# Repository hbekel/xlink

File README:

XLINK -- Bidirectional 8-bit parallel data transfers between PS/2
Parallel Port and C64 User Port with optional reset circuit

---------------------------------------------------------------------
Introduction
---------------------------------------------------------------------

XLINK is a system for fast 8-bit parallel data transfers between a C64
and an IBM-PC using a either a parallel port cable or a simple USB
device connected to the C64 user port.

A command-line client on the PC side is used to send data or commands
to an interrupt-driven server installed on the C64. It is possible to
load data from disk into C64 memory, save C64 memory content to disk,
to peek and poke values to and from C64 memory, run BASIC programs,
jump to memory addresses, and force a hardware reset of the C64.

Different options exists to install the server on the C64, from a
simple server.prg that needs to be loaded on the C64 prior to use, or
a permanent solution that integrates a server in a modified kernal or
a simple eprom cartridge.

The underlying communication protocol is implemented in a shared
library, allowing you to use and extend xlink's functionality for your
own programs.

----------------------------------------------------------------------
Cable
----------------------------------------------------------------------

The XLINK cable is a simple 8-bit parallel transfer cable connecting
the PC Parallel Port to the C64 User port.

       ---------------------------------------------
       PC Parallel Port   |     C64 User Port
       ---------------------------------------------
       GND    (18-25)    <->    GND    (1, 12, A, N)
       D0     (2)        <->    PB0    (C) 
       D1     (3)        <->    PB1    (D) 
       D2     (4)        <->    PB2    (E) 
       D3     (5)        <->    PB3    (F) 
       D4     (6)        <->    PB4    (H) 
       D5     (7)        <->    PB5    (J) 
       D6     (8)        <->    PB6    (K) 
       D7     (9)        <->    PB7    (L) 
       BUSY   (11)       <--    PA2    (M) 
       STROBE (1)        -->    /FLAG2 (B) 

A shielded cable is recommended. The cable shield should be connected
to shield ground on both sides. A 0.1uF capacitor between shield and
ground at the c64 side can also help to reduce noise. Improper
shielding will most likely cause transfer errors.

CAUTION: There is no protection of any kind. The parallel port pins
are directly connected to port B of CIA2. Always power down both the
PC and C64 before inserting/removing the cable. Also turn off the C64
during boot, reboot or shutdown of the PC.

----------------------------------------------------------------------
Optional Reset Circuit
----------------------------------------------------------------------

This small circuit can be used to force a hardware reset of the C64
when the INIT line at the parallel port is pulled low.
                  
 INIT                      +5V                          
  o                         o                                          
  |      ____               |                                  
  o-----|____|--------------o       o RESET                                    
  |      10k                |       |                                      
  |                 ____    |       |                                    
  |            ----|____|---'       |                                       
  |            |    1.5k            |                                   
  |            |                 |  C                        
  |            |                 | /                                       
  |         |  C-----------------|B                                             
  |  ____   | /                  | \                                            
  '-|____|--|B                   |  E                                          
     10k    | \                     |                       
            |  E                    |                                          
               |                    |                                       
               o                    o                                       
              GND                  GND                                      

INIT is pin 16 at the parallel port, RESET is pin 3 at the user port.
GND and +5V can safely be taken from the user port as well.
Use BC547A or equivalent transistors.

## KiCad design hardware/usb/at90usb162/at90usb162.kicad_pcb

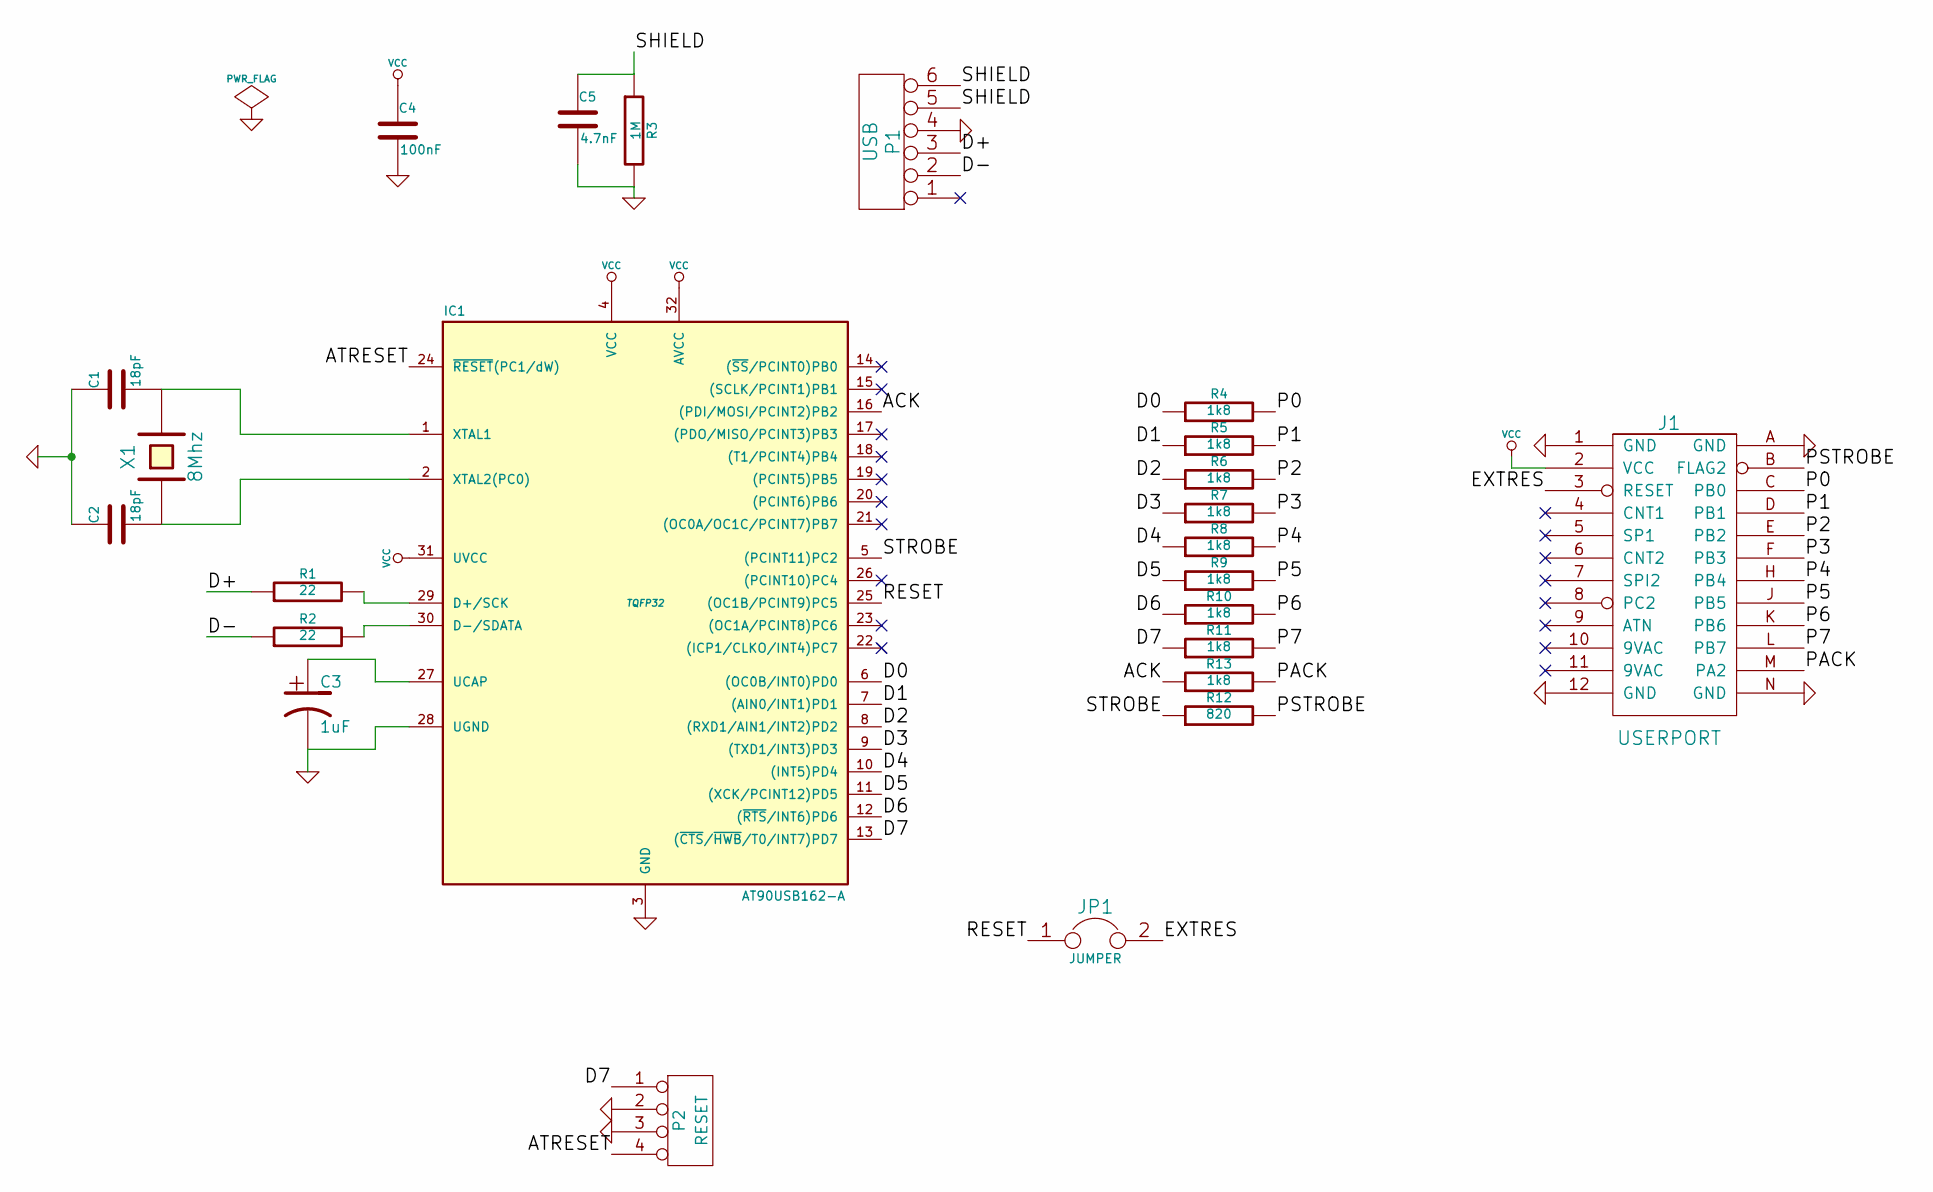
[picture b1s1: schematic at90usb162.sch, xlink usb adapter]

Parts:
C1, C2: 18pF
C3: 1uF
C4: 100nF
C5: 4.7nF
IC1: AT90USB162-A; TQFP32
J1: USERPORT
JP1: JUMPER
P1: USB
P2: RESET
R1, R2: 22
R3: 1M
R4, R5, R6, R7, R8, R9, R10, R11, R13: 1k8
R12: 820
X1: 8Mhz

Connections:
/ACK: IC1.16 ((PDI/MOSI/PCINT2)PB2), R13.1
/ATRESET: IC1.24 (~RESET~(PC1/dW)), P2.4
/D0: IC1.6 ((OC0B/INT0)PD0), R4.1
/D1: IC1.7 ((AIN0/INT1)PD1), R5.1
/D2: IC1.8 ((RXD1/AIN1/INT2)PD2), R6.1
/D3: IC1.9 ((TXD1/INT3)PD3), R7.1
/D4: IC1.10 ((INT5)PD4), R8.1
/D5: IC1.11 ((XCK/PCINT12)PD5), R9.1
/D6: IC1.12 ((~RTS~/INT6)PD6), R10.1
/D7: IC1.13 ((~CTS~/~HWB~/T0/INT7)PD7), P2.1, R11.1
/D+: P1.3, R1.1
/D-: P1.2, R2.1
/EXTRES: J1.3 (RESET), JP1.2
/P0: J1.C (PB0), R4.2
/P1: J1.D (PB1), R5.2
/P2: J1.E (PB2), R6.2
/P3: J1.F (PB3), R7.2
/P4: J1.H (PB4), R8.2
/P5: J1.J (PB5), R9.2
/P6: J1.K (PB6), R10.2
/P7: J1.L (PB7), R11.2
/PACK: J1.M (PA2), R13.2
/PSTROBE: J1.B (FLAG2), R12.2
/RESET: IC1.25 ((OC1B/PCINT9)PC5), JP1.1
/SHIELD: C5.1, P1.5, P1.6, R3.1
/STROBE: IC1.5 ((PCINT11)PC2), R12.1
GND: C1.1, C2.1, C3.2, C4.2, C5.2, IC1.3 (GND), IC1.28 (UGND), J1.1 (GND), J1.12 (GND), J1.A (GND), J1.N (GND), P1.4, P2.2, P2.3, R3.2
unnamed: IC1.30 (D-/SDATA), R2.2
unnamed: IC1.29 (D+/SCK), R1.2
unnamed: C3.1, IC1.27 (UCAP)
unnamed: C2.2, IC1.2 (XTAL2(PC0)), X1.1
unnamed: C1.2, IC1.1 (XTAL1), X1.2
VCC: C4.1, IC1.4 (VCC), IC1.31 (UVCC), IC1.32 (AVCC), J1.2 (VCC)

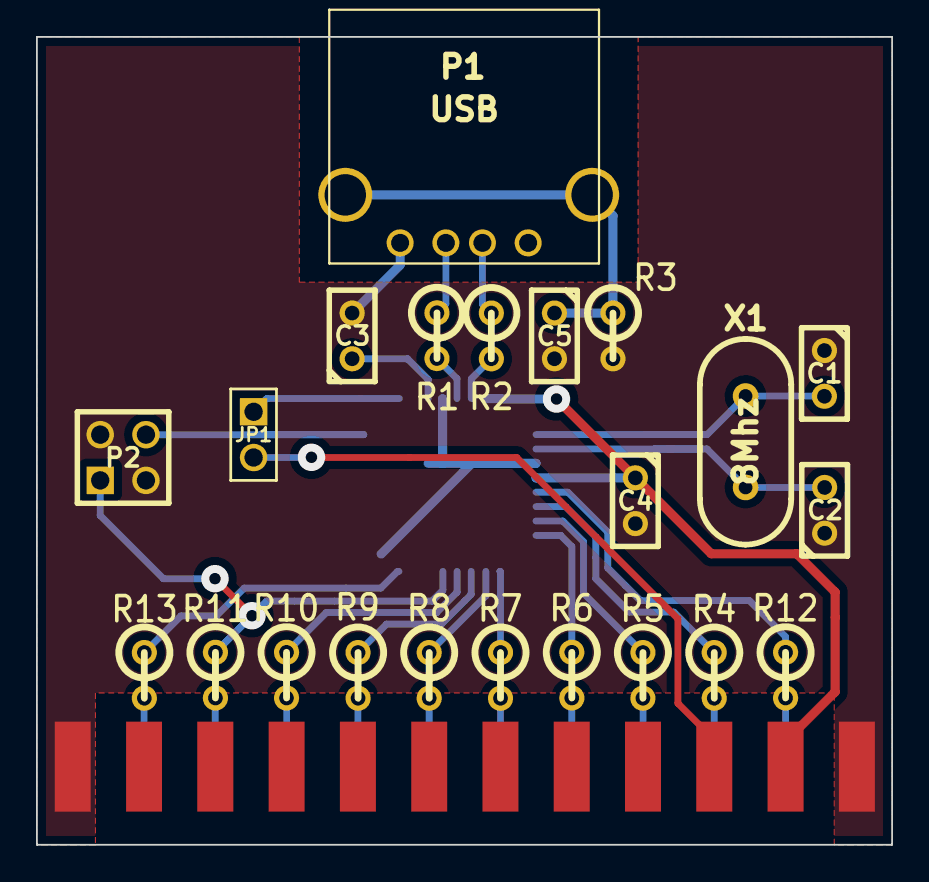
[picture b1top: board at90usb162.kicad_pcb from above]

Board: 2 copper layers, 47.5 x 44.9 mm, 23 parts (1 on the bottom side), 22 nets.

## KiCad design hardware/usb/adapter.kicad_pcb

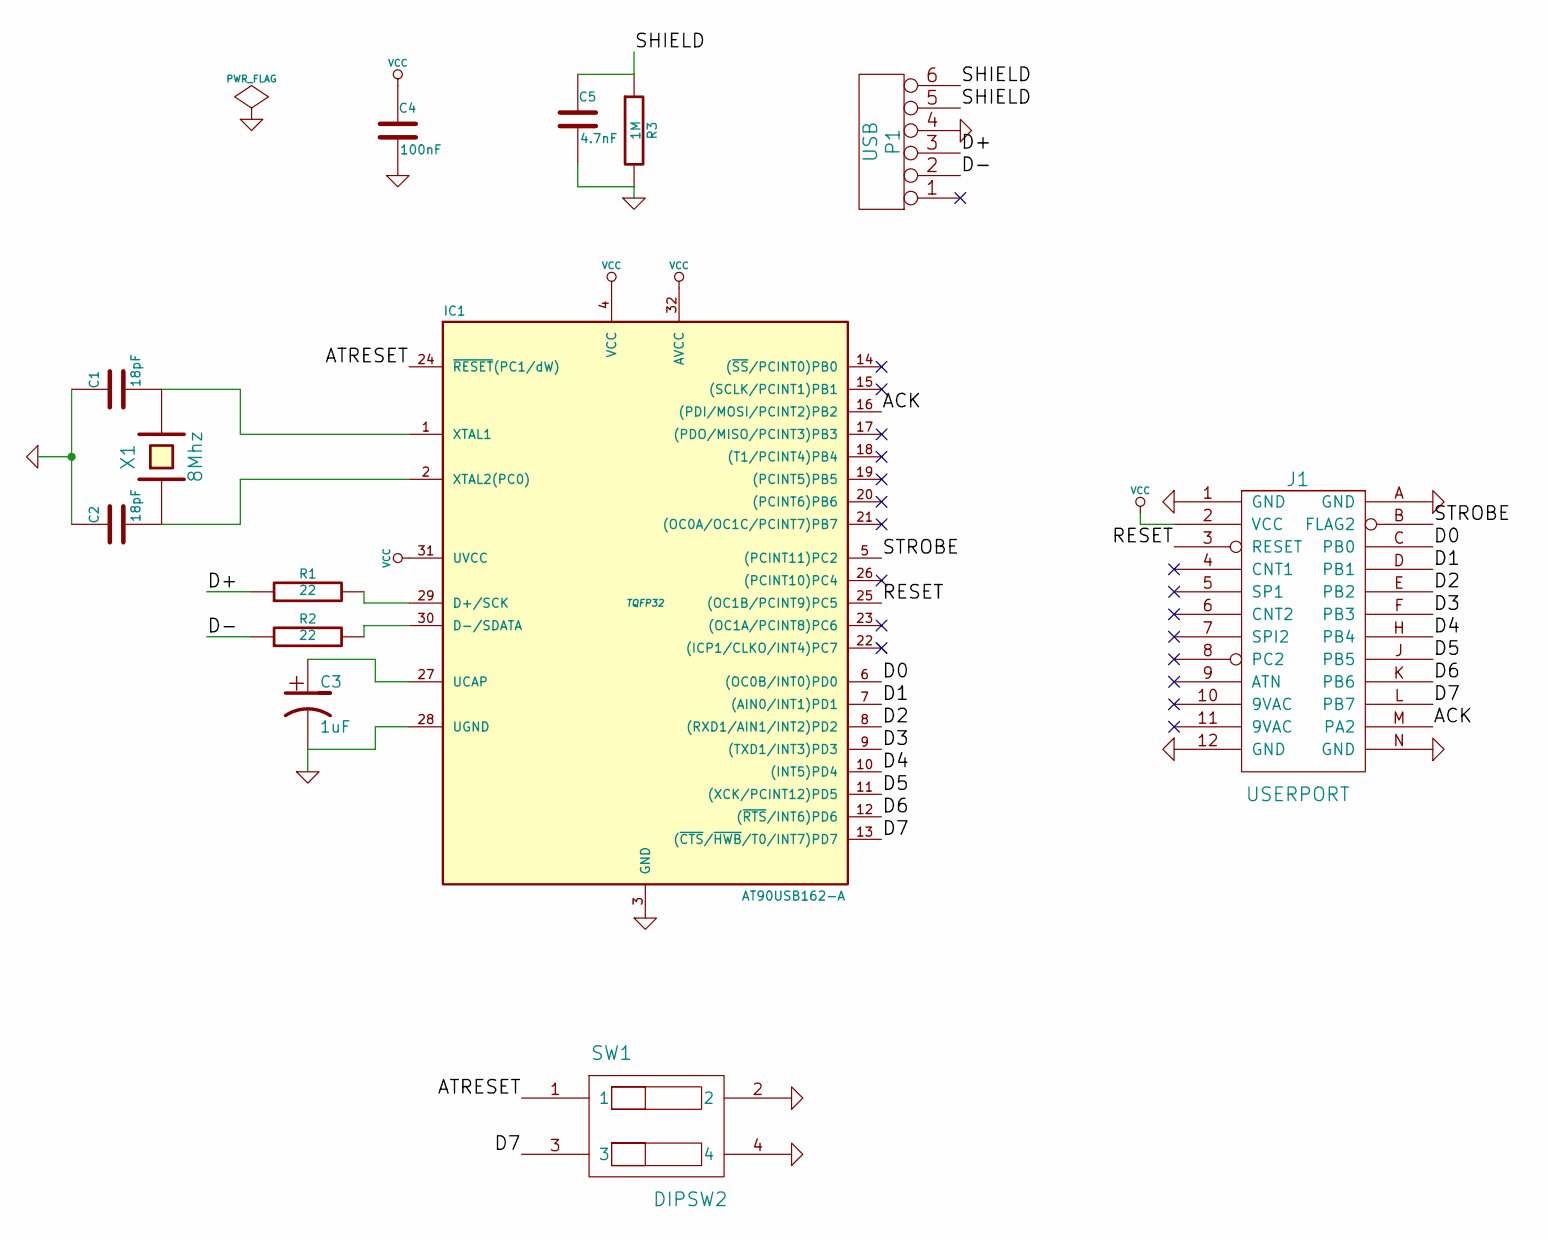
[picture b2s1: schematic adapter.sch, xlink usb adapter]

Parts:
C1, C2: 18pF
C3: 1uF
C4: 100nF
C5: 4.7nF
IC1: AT90USB162-A; TQFP32
J1: USERPORT
P1: USB
R1, R2: 22
R3: 1M
SW1: DIPSW2
X1: 8Mhz

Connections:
/ACK: IC1.16 ((PDI/MOSI/PCINT2)PB2), J1.M (PA2)
/ATRESET: IC1.24 (~RESET~(PC1/dW)), SW1.1
/D0: IC1.6 ((OC0B/INT0)PD0), J1.C (PB0)
/D1: IC1.7 ((AIN0/INT1)PD1), J1.D (PB1)
/D2: IC1.8 ((RXD1/AIN1/INT2)PD2), J1.E (PB2)
/D3: IC1.9 ((TXD1/INT3)PD3), J1.F (PB3)
/D4: IC1.10 ((INT5)PD4), J1.H (PB4)
/D5: IC1.11 ((XCK/PCINT12)PD5), J1.J (PB5)
/D6: IC1.12 ((~RTS~/INT6)PD6), J1.K (PB6)
/D7: IC1.13 ((~CTS~/~HWB~/T0/INT7)PD7), J1.L (PB7), SW1.3
/D+: P1.3, R1.1
/D-: P1.2, R2.1
/RESET: IC1.25 ((OC1B/PCINT9)PC5), J1.3 (RESET)
/SHIELD: C5.1, P1.5, P1.6, R3.1
/STROBE: IC1.5 ((PCINT11)PC2), J1.B (FLAG2)
GND: C1.1, C2.1, C3.2, C4.2, C5.2, IC1.3 (GND), IC1.28 (UGND), J1.1 (GND), J1.12 (GND), J1.A (GND), J1.N (GND), P1.4, R3.2, SW1.2, SW1.4
unnamed: IC1.30 (D-/SDATA), R2.2
unnamed: IC1.29 (D+/SCK), R1.2
unnamed: C3.1, IC1.27 (UCAP)
unnamed: C2.2, IC1.2 (XTAL2(PC0)), X1.1
unnamed: C1.2, IC1.1 (XTAL1), X1.2
VCC: C4.1, IC1.4 (VCC), IC1.31 (UVCC), IC1.32 (AVCC), J1.2 (VCC)

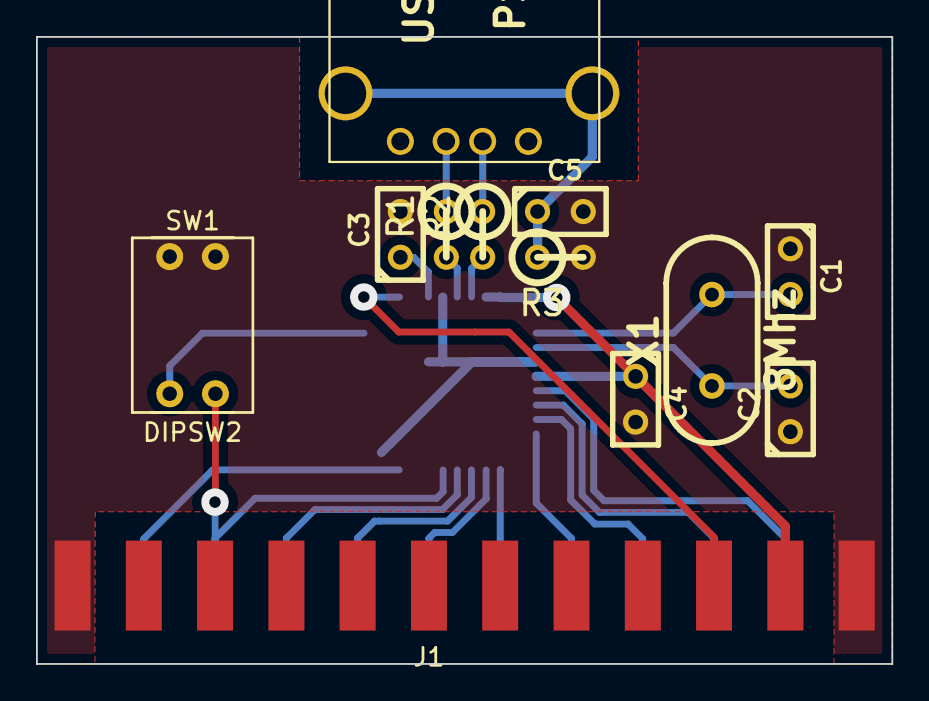
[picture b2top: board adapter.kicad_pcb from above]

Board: 2 copper layers, 47.5 x 34.8 mm, 13 parts (1 on the bottom side), 22 nets.

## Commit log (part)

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2012-11-27 Initial commit.
2012-12-01 Client: Fixed bug setting memory defaults; Server: optimized for speed, now reaching ~21kb/s
2012-12-02 Fixed relinkBasic routine, RRServer: properly read/write with custom memory config.
2012-12-06 Renamed c64link.(c|h|so) to pp64(c|h|so).
2012-12-13 Adjusted Retro Replay server to use BUSY line for ack and strobe signals.
2012-12-20 Kernal: Wedge from system irq service routine at $ea31 instead system irq entry.
    This enhance compatibility for games/demos using their own interrupt vector
    at $0314... since we ack any cia B interrupts, we should do it only in the default
    irq service routine.
2013-03-06 Separated Makefile into Makefile.linux and Makefile.cygwin, adjusted conditional compilation
2013-03-14 Fixed save routines in rrserver and kernal server (memory config in fast save)
2013-03-20 Windows: Build native MinGW-Win32 binary, statically link pp64.dll, Linux: removed cross compiled c64.exe target
    Removes dependency on cygwin1.dll and pp64.dll
2013-06-23 Fixed reading/writing binary files in windows, merged Makefiles, build an link pp64.dll for windows
2013-06-30 Fixed default device setting in server, added drive code to kernal, added drive status command, fixed parsing of dos command, added ready command, improved Makefile
2013-08-01 Added extension framework, reimplemented drive/dos commands as extensions
2013-08-01 Improved help command, code cleanups
2013-08-13 Added shell mode and StringList utility functions.
2013-09-14 Fixed bug in pp64_open() on windows (failure to init/return successfully when pp64_open is called successively despite inpout32 having been correctly loaded in the first call)
2013-12-07 Added missing verify command to shell completion list
2014-02-16 Added client default device "/dev/c64", reverted ping timeout to 250ms, removed signedness warnings
2014-02-22 Put windows specific code back into parport driver
2014-02-25 Client: replaced printf's with logging where apropriate
2014-07-09 Changed deprecated readline typedef CPPFunction to rl_completion_func_t
2014-07-16 Made run command with file argument run basic program or jump to load address for ml programs
2014-07-17 Catch unknown commands and abort with error, added error message to ready command
2014-07-30 Changed load semantics: added --skip option, removed reliance on file extensions
2014-08-10 Fixed segfault in lib when freeing null pointer (logger->context not initialized)
2014-08-27 Added missing DllMain function for windows dll, Fixed library initialization
    Need to test for driver->ready() after trying to setup the default USB device
    to determine whether to try the default parport device as a fallback.
2014-08-27 Added "boot" command to enter dfu-bootloader, Renamed "flash" to "boot" in driver and firmware
2014-08-28 Renamed firmware from "uuadapter" to "xlink"
2014-08-29 Kernal: Added skipping of memory tests, changed startup message
    - Implemented a fake memory test that simply checks for a cartridge and
    sets the memory top accordingly
    - Changed startup message to "C64 BASIC V2 XLINK V1"
2014-08-29 Added License
2014-08-29 Don't free the driver after failed driver_setup(), let driver->ready also fail when no open function has been assigned.
2014-09-01 Added a simple server for bootstraping, generate a basic loader for it
2014-09-02 Library: either use the user supplied XLINK_DEVICE or try the default devices on initialisation
2014-09-02 Improved documentation
2014-09-03 Fixed typo in bootstrap.bas, code cleanups
2014-09-04 Hardsid.dll: Added configuraiton via env vars, delegate legacy interface
    Environment Vars:
    XLINK_HARDSIDS=<address>[,<address]...]
    XLINK_HARDSID_DEBUG=[0|1]
2014-09-04 Benchmark: abort unless xlink_ready(), Makefile: less verbose output
2014-09-05 Servers: Improved readability, added separators
2014-09-06 Bootstrap: code cleanup
2014-09-12 Makefile: sleep for 5 seconds after entering bootloader
2014-09-13 Hardsid: Reset all sids
2014-09-14 Hardsid: Removed 2.00+ Interface for goattracker, still futile
2014-09-23 Added identify command to clients online documentation
2014-09-24 Server, Kernal: Added Server namespace containing the respective identification values
2014-09-25 Documentation: Started to write manual/website
2014-09-28 Client, Makefile: Compile fixes and code cleanups
2014-09-30 Fixed: Failed to properly detect missing identification support in server
2014-10-03 Driver: (Linux) Log error message if the device node does not point to a USB device
2014-10-07 USB: Ported to libusb-1.0
2014-10-08 Makefile: Added $PREFIX, $DESTDIR and $SYSCONFDIR to ease packaging
2014-10-08 Driver: Code cleanups
2014-10-09 Library: Renamed XLinkServerInfo struct to xlink_server
2014-10-10 Library: Refactored all error handling to use xlink_error reporting
2014-10-11 Some code cleanups, refined logging
2014-10-17 Driver: Simplified device type identification based on major numbers
    Removes redundant log messages when setting up the device driver
2014-10-31 Server: Jump directly to sysirq after handling command
2014-11-04 Library/Client: added extension to relocate server (simple load and jump), added xlink_relocate, adjusted client, added relocation attempts before load and poke
2014-11-05 Library: Added memtop to xlink_server_info, used to determine range of lower memory for relocation
2014-11-05 Client: relocate ram-based server to $c000 for benchmark command
2014-11-05 Client: Cleaned up help text
2014-11-06 Server: identify: use write subroutine instead of macro (optimize size)
2014-11-06 Client: Improved help texts
2014-11-07 Library: Fixed xlink_identify return value (true event if driver->open() failed)
2014-11-08 Bootstrap: Simplified bootstraping (load runnable server, so it can be saved via basic save commands)
2014-11-10 Firmware: VID, PID, SERIAL to atmega8 from env vars, define MANUFACTURER and PRODUCT for both in main Makefile
2014-11-21 Hardware: moved at90usb162 to subdirectory
2015-01-28 Hardware: Moved crystal to avoid possible short between oscillator case and VCC trace
2015-02-03 Hardware: Enlarged board to increase stability of usb socket
2015-02-04 Library/Client: Windows: Enhanced feedback if inpout32 driver is not installed
2015-02-16 Hardware: Removed copper island, improved routing
2015-02-18 Makefile: Adjusted for linux builds, should stay the default for releases
2015-03-01 Library: Started cleaning up xlink.h, remove everything not strictly required by users
2015-03-02 Library: Fixed error in xlink_ready() (introduced in last commit)
2015-03-03 Client: Cosmetic changes
2015-03-08 Server: Jump: Fixed for code that does an RTS back to basic
2015-03-13 Client: added saving of history file from shell mode
    500 lines of shell history are kept at ~/.xlink_history
2015-03-13 Library/Client: added function/command to fill memory area with byte
2015-03-14 Library: Removed xlink_fill() from library, implemented as command only
    Trying to keep the public api as simple as possible...
2015-03-17 Client: Changed "fill" command syntax to "fill <range> <value>"
    The address range is a required argument, not an option.
2015-03-18 Library: Added low-level functions xlink_send() and xlink_receive()
    These can be used in conjunction with xlink_inject() to implement
    custom communication schemes.
2015-03-25 Library: Removed useless debug messages
2015-03-27 Library/Firmware: Use 1d50:60c8 vid/pid kindly provided by OpenMoko, Inc
    Thanks OpenMoko :)
2015-03-28 Kernal: Fixed bug that prevented basic SAVE from working
2015-04-02 Library: Improved lowlevel interface with automatic direction handling
    The new functions xlink_begin and xlink_end() must now be used to
    intiate or terminate a communication session with an injected custom
    server. After xlink_begin() the first call to either send() or
    receive() will not require any handshaking, but all subsequent calls
    until xlink_end() will require a handshake if the transfer direction
    changes. This simplifies writing of server routines and assures proper
2015-04-02 Client: Removed shell, don't link readline (licensing)
    And I thought readline was LGPL...
2015-04-02 Library: Added resource file for win32 dll build
2015-04-13 Parport: Initial read of ack state only, adjusted timeout to match usb timeout
2015-04-29 Library: Fixed: Added missing exports in xlink.lib file
2015-05-13 Server: Added simple c128 ram based server, implemented load, run & identify
2015-05-19 Library/Server: Fixed drive commands for shm/vice emulation
2015-05-22 Server/Client: Continued work on multiple machine support (c128)
    Integrated the ram based c128 server into the client
    Added --machine option to choose machine type (C64/C128)
    Also added support for XLINK_MACHINE environment variable
    Changed bank/mmu handling: --memory -> $ff00, --bank -> predefined banks
    Added reinstall stub at $1900/6400 to reinstall server after run/restore
    Abstracted machine differences, removed (almost) all hardcoded values
2015-05-25 C128: Kernal: Added identify command
2015-05-27 Server: C128: optimized load/save for mmu configurations where io is still available
    Also some minor code cleanups for C64 server
2015-05-29 Client: Updated/Improved online help
2015-06-02 Client: Minor improvements to help texts
2015-06-04 Library: Reset: Added another 250ms timeout after first ping response
    After a reset, we need to wait a little more after the first successfull
    ping because basic initialization might prevent the next ping from being
    served in time.
    Also added some more debug statements to xlink_ready().
2015-06-20 Sleep another 100ms after initial reset in xlink_ready()
2015-06-29 Servant64: Added chunked writes with intermediate tcdrain() calls (untested)
    This will be required to increase the baud rate above 115200bps...
2015-07-08 Kernal64: Fixed crash on tape save, adjusted message for tape load/save
2015-07-15 Library/Client: Removed all disk drive commands and functionality
    The disk drive commands have never worked reliably or fast enough and
    have bloated the code of both the client and library, and have therefore
    been removed entirely.
    A proper disk backup tool might be created in the future. Such a tool
    would need to use proper fastloading and -saving, error handling and
    reproduction and support for more than the standard 35 tracks to be truly
2015-08-08 Client/Library: Refactored for clang, added support for macosx
    Removed all nested functions (non-standard gnu extension), refactored
    using either macros or by passing around context.
    This version builds on macosx and works at least with the USB adapter.
    The shm and servant drivers still need to be tested.
    Building with clang under Linux should work now, too.
    Adjusted the Makefile to build using $CC, determing the shared lib file
2015-08-14 Library: Disabled experimental servant64 driver until further notice
2015-09-27 Firmware: Increase time FLAG2 line is held low (fix for C64C boards)
    The FLAG2 line needs to be held low for more than 250ns on later boards
    (beginning with assy 250469) because a 470pf Capacitor(C6) has been added.
    A delay of 6 NOP operations has been added to compensate, and results in
    proper operation with later boards.
2015-10-05 Makefile: Explicitly set bash as the shell used by make
    The Makefile requires the bash builtin "let" while make uses /bin/sh
    by default. On systems where /bin/sh is not bash, the build thus
    fails.
    Need to check whether let is needed at all or whether it can be
    replaced with bourne-compatible statement.
2016-01-26 Library: Fixed typo breaking the build on linux
2020-08-25 Added gerber files, please read WARNING.txt before using them
2022-09-07 Fixed windows build, switched to building 64bit windows version
    - Use -I/usr/$(MINGW32)/include instead of -I/usr/include, else headers
    get mixed up between the system and mingw
    - Use inpout64.dll instead of inpout32.dll
    - Fixed formatting
    enter the commit message for your changes. Lines starting
2022-09-18 Makefile: Back to 32bit build, added msi generation using wixl
